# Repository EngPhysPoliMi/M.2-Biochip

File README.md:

# M.2 - Biochip

Repository for "Biochip".

## Use instructions

To make it truly accessible to anyone, here's an easy introduction to GitHub.

### Accessing materials

Not all files can be previewed on the GitHub page, but there is always the possibility to download them on your device.

#### Downloading a single file

1) Navigate to the file using the repository explorer above.
2) Click on the file.
3) On the right side of the file view, look for the “Download” button, or simply click on the "Raw" button, then right-click and select "Save As..." to save the file to your device.

#### Downloading the entire repository

1) On the main page of the repository, look for the green "Code" button.
2) Click on it and select "Download ZIP". This will download the entire repository as a compressed file.
3) Extract the ZIP file on your device to access the contents.

### Contributing

You might want to add a file, update one, change a name, open a repository about a new subject of the course, structure a repository differently, or something else entirely.
To do that, you have to open an issue that ultimately must be approved (resolved) by an admin.

Changes to the structure, i.e. opening a repository or the ordering of directories, must be requested on [this](https://github.com/EngPhysPoliMi/Homepage) page, to be considered the main repository.

Changes to files and local directories must be requested directly on the subject repository.

Advanced users can choose to make a "pull request" but it's arbitrary.

#### Requesting Changes

If you notice any mistakes or think that something should be updated in the notes, please feel free to report it following these steps:

1) Click on the "Issues" tab at the top of the repository.
2) Click on "New Issue".
3) Describe the change you'd like to see, and provide as much detail as possible. Click "Submit" when you’re done.

#### Requesting the Upload of a New File

To request the addition of a new file or resource, follow these steps:

1) Open an Issue: As with requesting a change, click the "Issues" tab.
2) Click "New Issue".
3) Drag and drop the file in the issue description with a short definition of what's being added. Click "Submit" when you’re done.

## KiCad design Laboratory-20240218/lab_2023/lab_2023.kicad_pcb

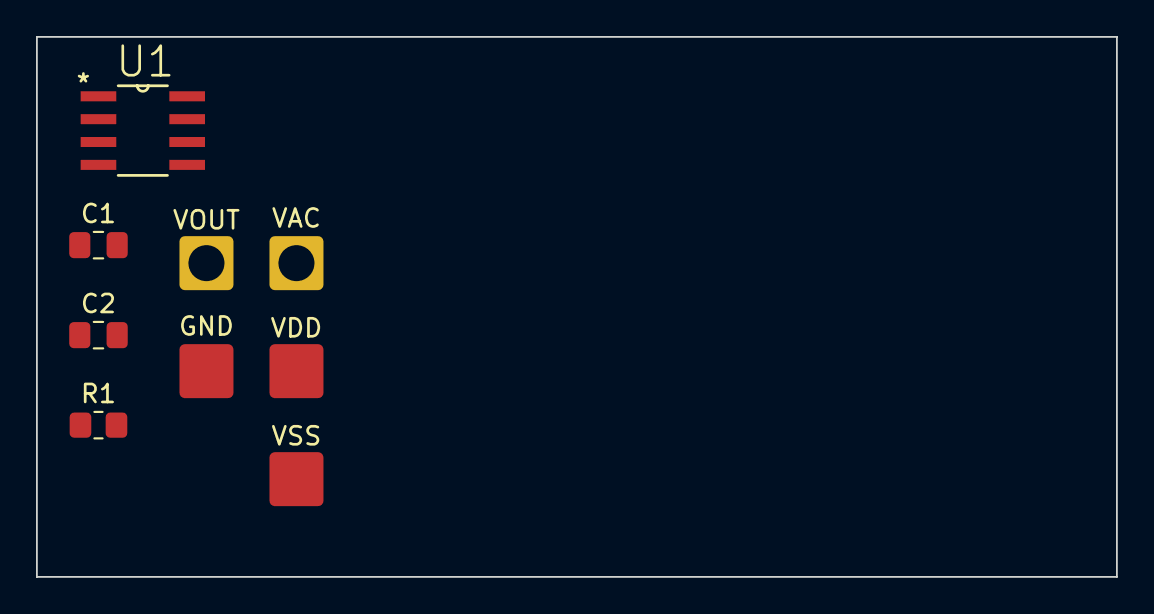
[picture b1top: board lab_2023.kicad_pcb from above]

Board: 2 copper layers, 60.0 x 30.0 mm, 9 parts (0 on the bottom side), 5 nets, no tracks yet.

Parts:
C1, C2: 100n; C_0805_2012Metric_Pad1.18x1.45mm_HandSolder
GND: Conn_01x01_Female; PAD_NOHOLE
R1: R; R_0805_2012Metric_Pad1.20x1.40mm_HandSolder
U1: AD8022ARZ; SOIC127P600X175-8N
VAC: Conn_01x01_Female; PAD_HOLE
VDD: Conn_01x01_Female; PAD_NOHOLE
VOUT: Conn_01x01_Female; PAD_HOLE
VSS: Conn_01x01_Female; PAD_NOHOLE

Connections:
/I_IN: R1.1, U1.2 (-IN1)
/VDD: C1.2, U1.8 (+VS), VDD.1
/VOUT: R1.2, U1.1 (OUT1), VOUT.1
/VSS: C2.2, U1.4 (-VS), VSS.1
GND: C1.1, C2.1, GND.1, U1.3 (+IN1)

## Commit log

2026-03-14 primo
